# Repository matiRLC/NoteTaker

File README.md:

# NoteTaker
PS/2 Keyboard with an attached LCD screen and a thermal printer.
Project inspired by PHG, Lima - Peru

Project Video:
https://www.youtube.com/watch?v=QOl3Mw9ThZ8

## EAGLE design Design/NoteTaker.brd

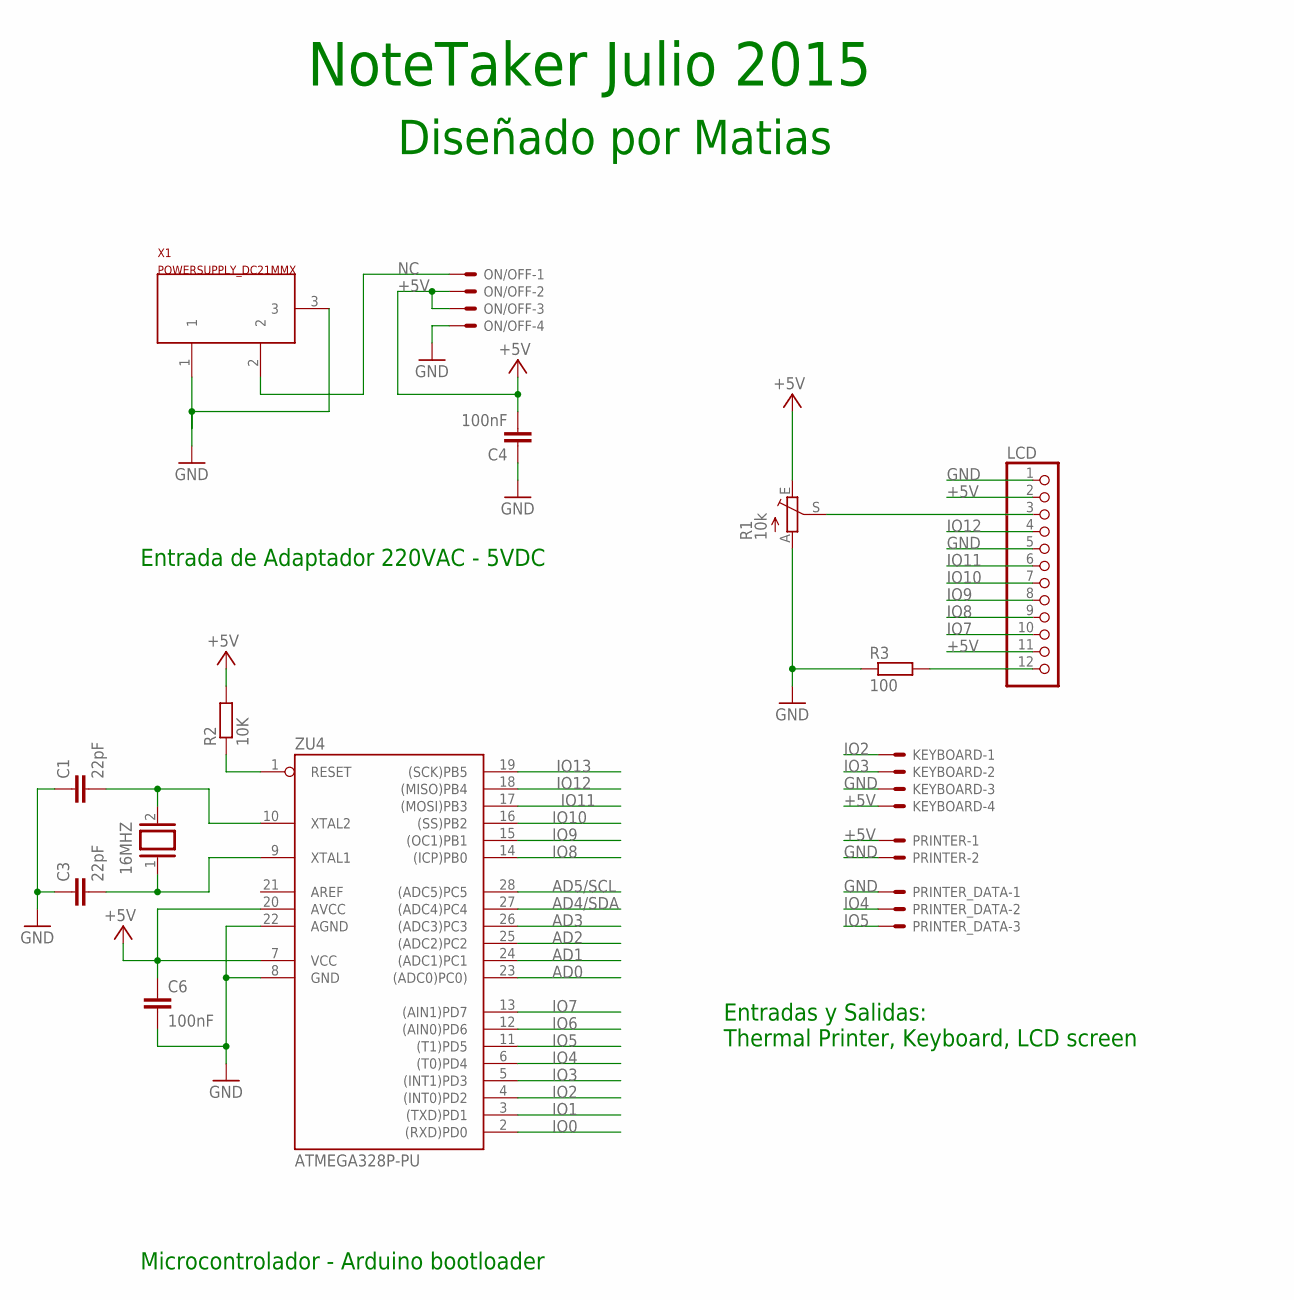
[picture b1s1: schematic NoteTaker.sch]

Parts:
16MHZ: XTAL/S; QS
C1, C3: 22pF; C025-025X050
C4, C6: 100nF; C025-025X050
KEYBOARD: KK-156-4
LCD: PINHD-1X12; 1X12
ON/OFF: KK-156-4
PRINTER: KK-156-2
PRINTER_DATA: KK-156-3
R1: 10k; S64W
R2: 10K; 0207/10
R3: 100; 0207/10
X1: POWERSUPPLY_DC21MMX; POWERSUPPLY_DC-21MM
ZU4: ATMEGA328P-PU; DIL28-3

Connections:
+5V: C4.2, C6.1, KEYBOARD.4, LCD.2, LCD.11, ON/OFF.2, ON/OFF.3, PRINTER.1, R1.E, R2.2, ZU4.7 (VCC), ZU4.20 (AVCC)
AD0: ZU4.23 ((ADC0)PC0))
AD1: ZU4.24 ((ADC1)PC1)
AD2: ZU4.25 ((ADC2)PC2)
AD3: ZU4.26 ((ADC3)PC3)
AD4/SDA: ZU4.27 ((ADC4)PC4)
AD5/SCL: ZU4.28 ((ADC5)PC5)
GND: C1.1, C3.1, C4.1, C6.2, KEYBOARD.3, LCD.1, LCD.5, ON/OFF.4, PRINTER.2, PRINTER_DATA.1, R1.A, R3.1, X1.1, X1.3, ZU4.8 (GND), ZU4.22 (AGND)
IO0: ZU4.2 ((RXD)PD0)
IO1: ZU4.3 ((TXD)PD1)
IO2: KEYBOARD.1, ZU4.4 ((INT0)PD2)
IO3: KEYBOARD.2, ZU4.5 ((INT1)PD3)
IO4: PRINTER_DATA.2, ZU4.6 ((T0)PD4)
IO5: PRINTER_DATA.3, ZU4.11 ((T1)PD5)
IO6: ZU4.12 ((AIN0)PD6)
IO7: LCD.10, ZU4.13 ((AIN1)PD7)
IO8: LCD.9, ZU4.14 ((ICP)PB0)
IO9: LCD.8, ZU4.15 ((OC1)PB1)
IO10: LCD.7, ZU4.16 ((SS)PB2)
IO11: LCD.6, ZU4.17 ((MOSI)PB3)
IO12: LCD.4, ZU4.18 ((MISO)PB4)
IO13: ZU4.19 ((SCK)PB5)
unnamed: 16MHZ.1, C3.2, ZU4.9 (XTAL1)
unnamed: LCD.3, R1.S
unnamed: R2.1, ZU4.1 (RESET)
unnamed: LCD.12, R3.2
NC: ON/OFF.1, X1.2
XTAL2: 16MHZ.2, C1.2, ZU4.10 (XTAL2)

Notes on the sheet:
NoteTaker Julio 2015
Diseñado por Matias
Entrada de Adaptador 220VAC - 5VDC
Entradas y Salidas: Thermal Printer, Keyboard, LCD screen
Microcontrolador - Arduino bootloader

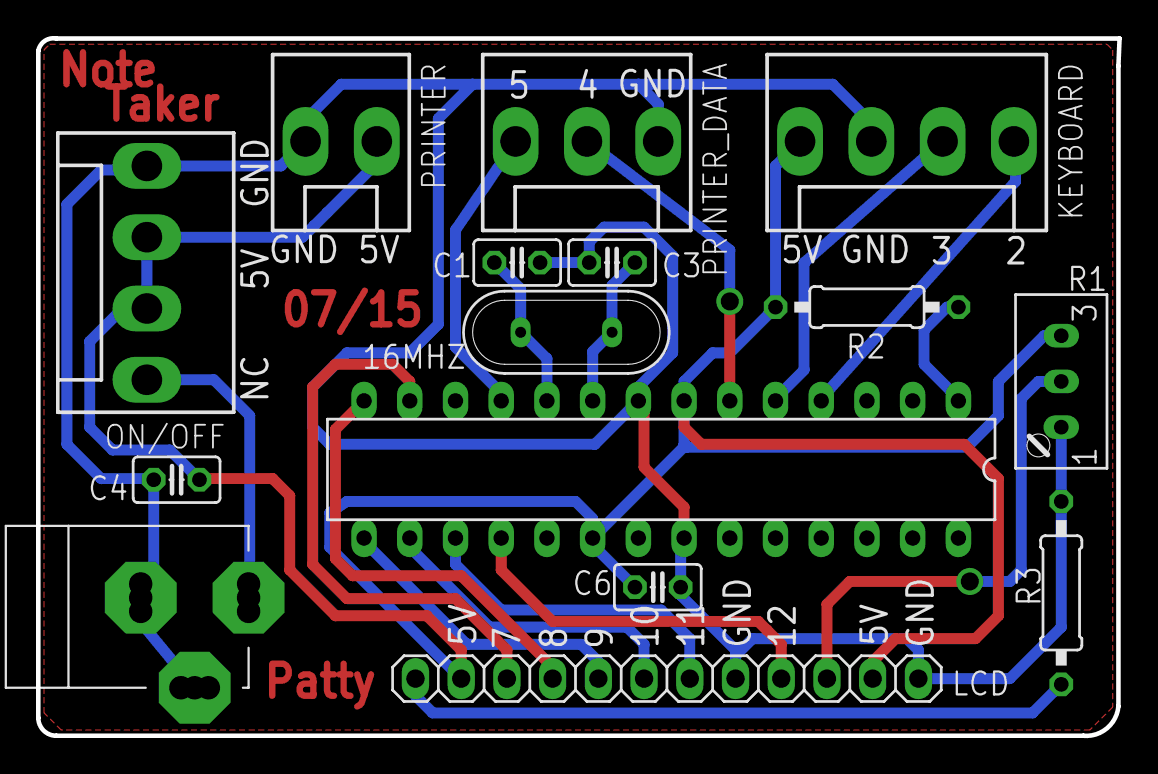
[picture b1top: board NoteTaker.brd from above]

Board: 2 copper layers, 60.1 x 38.8 mm, 15 parts (0 on the bottom side), 18 nets.

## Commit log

2018-05-27 rearranged file structure
2018-05-27 Track dock files
